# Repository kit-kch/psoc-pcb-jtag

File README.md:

# PSoC JTAG Adapter PCB

This repository contains schematic and layout for the PSoC JTAG adapter PCB.
It is meant to be used with the [main PSoC FMC PCB](https://github.com/kit-kch/psoc-pcb-fmc) and a [Digilent JTAG HS2](https://digilent.com/shop/jtag-hs2-programming-cable/?srsltid=AfmBOorvOwsRU_3dW2jPg2jQcidQeIOP8MnjYPq41F86tJ_p7KsCbM9X) to provide easy access to the programming interface.

The following parts have been used to manufacture the PCB, but compatible ones should work as well:

| Reference | Vendor   | Part               |
|-----------|----------|--------------------|
| J1        | samtec   | SSM-120-F-DV       |
| J2        | 3M       | D2540-6V0C-AR-WG   |
| J3        | Adam Tech| PH1RB-06-UA        |

For more information, refer to the psoc project website at [kch.dev/psoc](https://kch.dev/psoc).

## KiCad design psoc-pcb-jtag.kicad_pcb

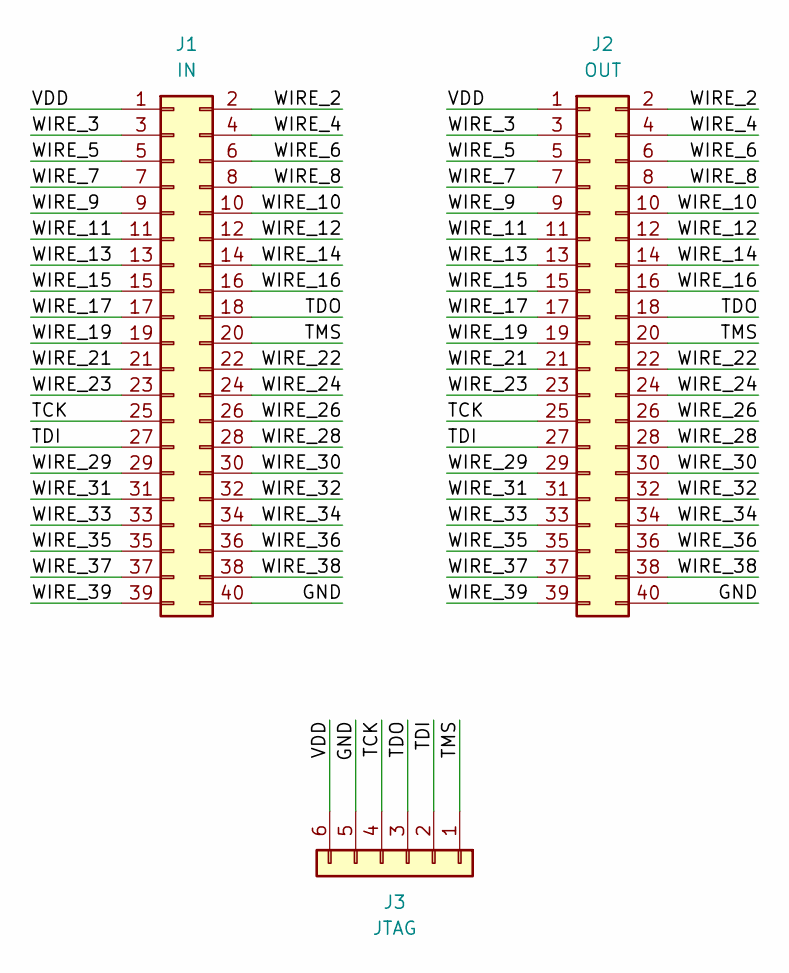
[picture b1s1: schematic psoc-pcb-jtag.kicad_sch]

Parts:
J1: IN; PinSocket_2x20_P2.54mm_Vertical_SMD
J2: OUT; IDC-Header_2x20_P2.54mm_Vertical_SMD
J3: JTAG; PinHeader_1x06_P2.54mm_Horizontal

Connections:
/GND: J1.40, J2.40, J3.5
/TCK: J1.25, J2.25, J3.4
/TDI: J1.27, J2.27, J3.2
/TDO: J1.18, J2.18, J3.3
/TMS: J1.20, J2.20, J3.1
/VDD: J1.1, J2.1, J3.6
/WIRE_2: J1.2, J2.2
/WIRE_3: J1.3, J2.3
/WIRE_4: J1.4, J2.4
/WIRE_5: J1.5, J2.5
/WIRE_6: J1.6, J2.6
/WIRE_7: J1.7, J2.7
/WIRE_8: J1.8, J2.8
/WIRE_9: J1.9, J2.9
/WIRE_10: J1.10, J2.10
/WIRE_11: J1.11, J2.11
/WIRE_12: J1.12, J2.12
/WIRE_13: J1.13, J2.13
/WIRE_14: J1.14, J2.14
/WIRE_15: J1.15, J2.15
/WIRE_16: J1.16, J2.16
/WIRE_17: J1.17, J2.17
/WIRE_19: J1.19, J2.19
/WIRE_21: J1.21, J2.21
/WIRE_22: J1.22, J2.22
/WIRE_23: J1.23, J2.23
/WIRE_24: J1.24, J2.24
/WIRE_26: J1.26, J2.26
/WIRE_28: J1.28, J2.28
/WIRE_29: J1.29, J2.29
/WIRE_30: J1.30, J2.30
/WIRE_31: J1.31, J2.31
/WIRE_32: J1.32, J2.32
/WIRE_33: J1.33, J2.33
/WIRE_34: J1.34, J2.34
/WIRE_35: J1.35, J2.35
/WIRE_36: J1.36, J2.36
/WIRE_37: J1.37, J2.37
/WIRE_38: J1.38, J2.38
/WIRE_39: J1.39, J2.39

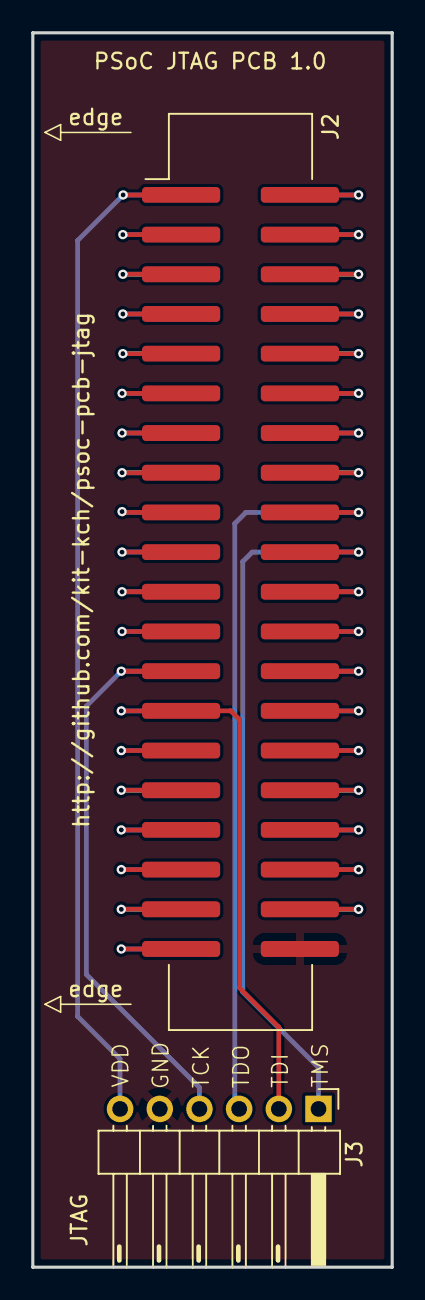
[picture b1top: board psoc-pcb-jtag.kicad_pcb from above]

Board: 2 copper layers, 23.0 x 79.0 mm, 3 parts (1 on the bottom side), 40 nets.

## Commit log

2025-07-18 README: Fix render image
2025-07-18 Add LICENSE
